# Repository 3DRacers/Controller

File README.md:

# 3DRacers Controller

The Arduino-powered controller for a 3DRacers.

This project is actually unsupported by the main development of 3DRacers, while exhist some valid alternatives:

 - A Bluetooth HID generic controller (like the cheap Android/iOS controllers available on the market)
 - A Bluetooth HID Arduino board like the Adafruit Bluefruit EZ-Key or the RedBearLab Blend Micro
 - A 3D printed remote attached to your smartphone
 
 For info about 3dracers: [www.3dracers.com](http://www.3dracers.com)
 For the 3DRacers Pilot Board schematics: [Pilot repository](https://github.com/3DRacers/PilotBoard)

License
----

Creative Commons Share-Alike 4.0

**Open Hardware, Hell Yeah!**

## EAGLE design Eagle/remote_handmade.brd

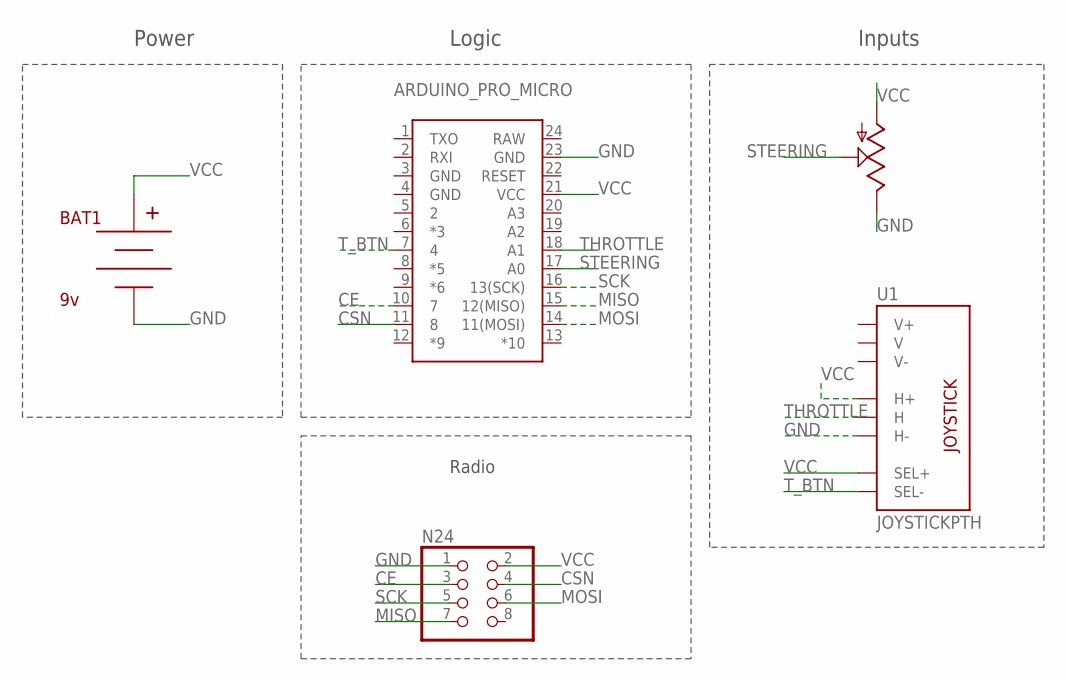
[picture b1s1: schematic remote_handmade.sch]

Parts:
ARDUINO_PRO_MICRO: ARDUINO_PRO_MICRONORMALNORMAL; ARDUINO_PRO_MICRO
BAT1: 9v; BC9VPC
N24: NRF24; 2X04
RV1: POT; ALPS_POT
U1: JOYSTICKPTH; JOYSTICK

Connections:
CE: ARDUINO_PRO_MICRO.10 (7), N24.3
CSN: ARDUINO_PRO_MICRO.11 (8), N24.4
GND: ARDUINO_PRO_MICRO.23 (GND), BAT1.V-, N24.1, RV1.P$1 (E), U1.H3 (H-)
MISO: ARDUINO_PRO_MICRO.15 (12(MISO)), N24.7
MOSI: ARDUINO_PRO_MICRO.14 (11(MOSI)), N24.6
SCK: ARDUINO_PRO_MICRO.16 (13(SCK)), N24.5
STEERING: ARDUINO_PRO_MICRO.17 (A0), RV1.P$2 (S)
THROTTLE: ARDUINO_PRO_MICRO.18 (A1), U1.H2 (H)
T_BTN: ARDUINO_PRO_MICRO.7 (4), U1.B2A (SEL-)
VCC: ARDUINO_PRO_MICRO.21 (VCC), BAT1.V+, N24.2, RV1.P$3 (A), U1.B1A (SEL+), U1.H1 (H+)

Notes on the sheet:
Power
Logic
Inputs
Radio

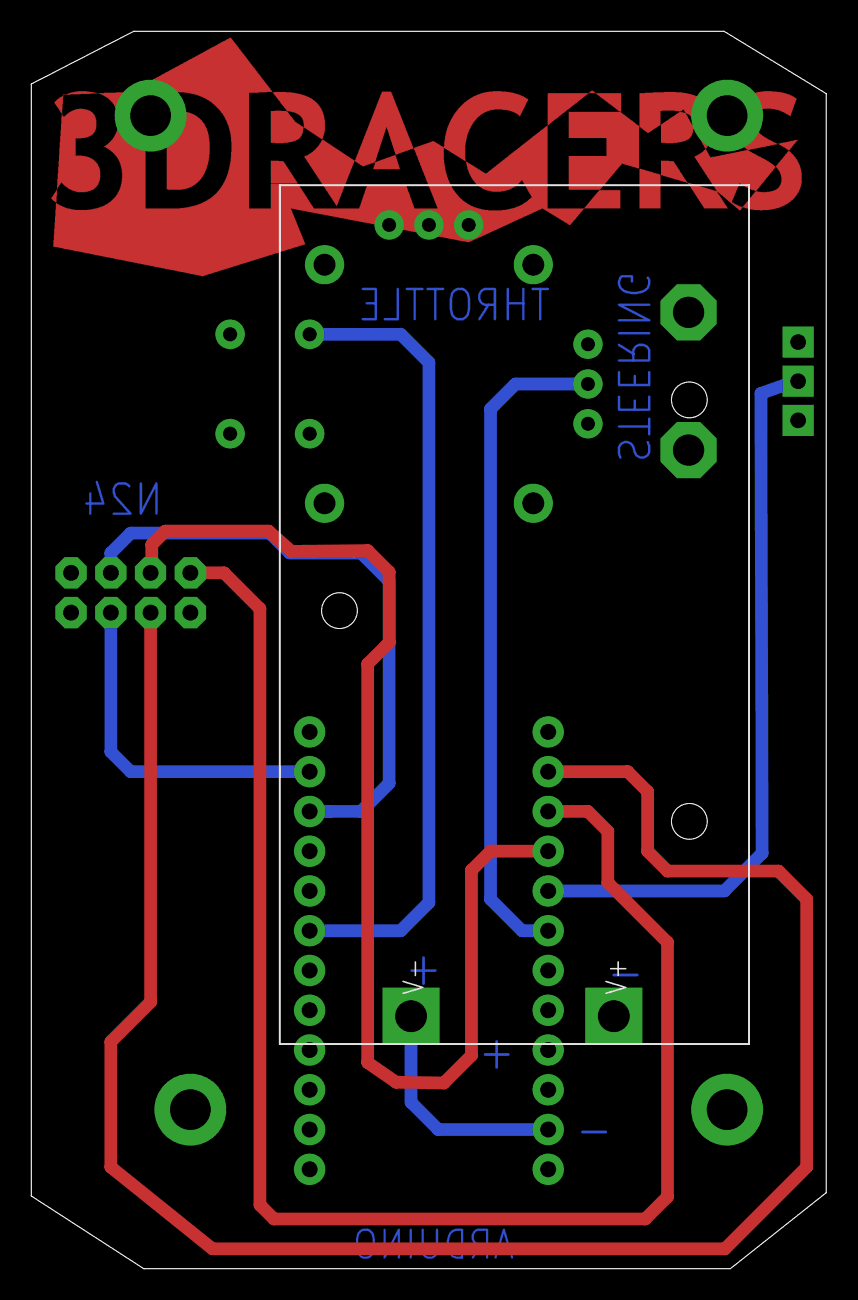
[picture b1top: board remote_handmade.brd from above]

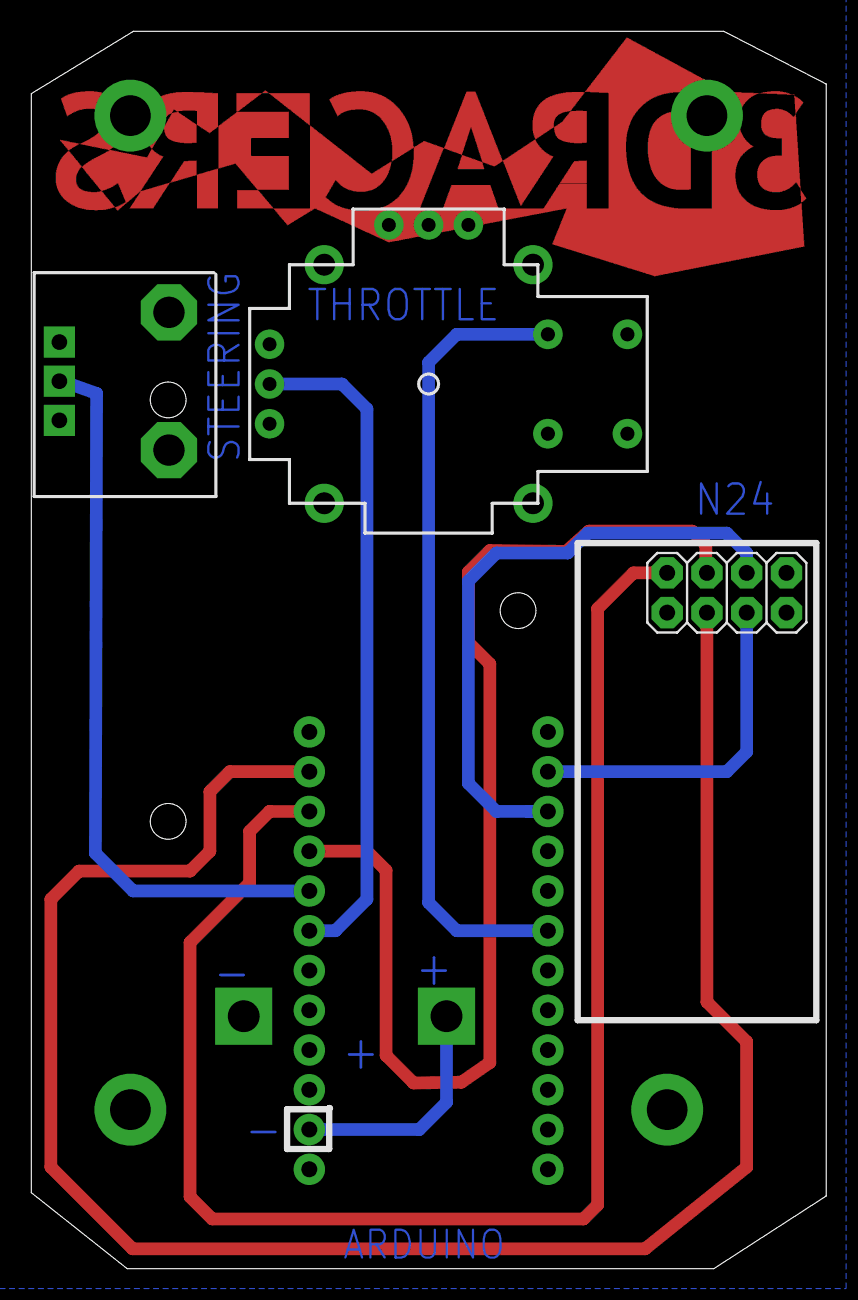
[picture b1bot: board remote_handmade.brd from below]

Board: 2 copper layers, 50.8 x 79.0 mm, 5 parts (3 on the bottom side), 10 nets.

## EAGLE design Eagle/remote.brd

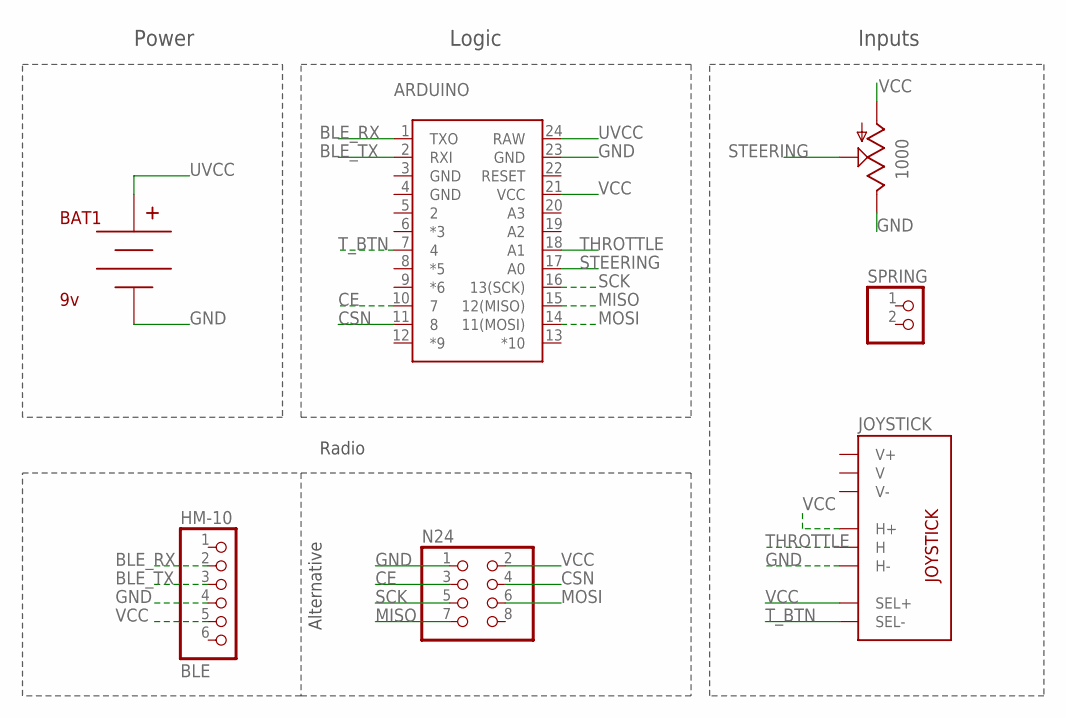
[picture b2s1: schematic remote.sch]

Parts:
ARDUINO: ARDUINO_PRO_MICRONORMALNORMAL; ARDUINO_PRO_MICRO
BAT1: 9v; BC9VPC
HM-10: BLE; 1X06-BIG
JOYSTICK: JOYSTICK
N24: NRF24; 2X04
RV1: 1000; ALPS_POT_2
SPRING: PINHD-1X2; 1X02

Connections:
BLE_RX: ARDUINO.1 (TXO), HM-10.2
BLE_TX: ARDUINO.2 (RXI), HM-10.3
CE: ARDUINO.10 (7), N24.3
CSN: ARDUINO.11 (8), N24.4
GND: ARDUINO.23 (GND), BAT1.V-, HM-10.4, JOYSTICK.H3 (H-), N24.1, RV1.P$1 (E)
MISO: ARDUINO.15 (12(MISO)), N24.7
MOSI: ARDUINO.14 (11(MOSI)), N24.6
SCK: ARDUINO.16 (13(SCK)), N24.5
STEERING: ARDUINO.17 (A0), RV1.P$2 (S)
THROTTLE: ARDUINO.18 (A1), JOYSTICK.H2 (H)
T_BTN: ARDUINO.7 (4), JOYSTICK.B2A (SEL-)
UVCC: ARDUINO.24 (RAW), BAT1.V+
VCC: ARDUINO.21 (VCC), HM-10.5, JOYSTICK.B1A (SEL+), JOYSTICK.H1 (H+), N24.2, RV1.P$3 (A)

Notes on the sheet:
Power
Logic
Inputs
Radio
Alternative

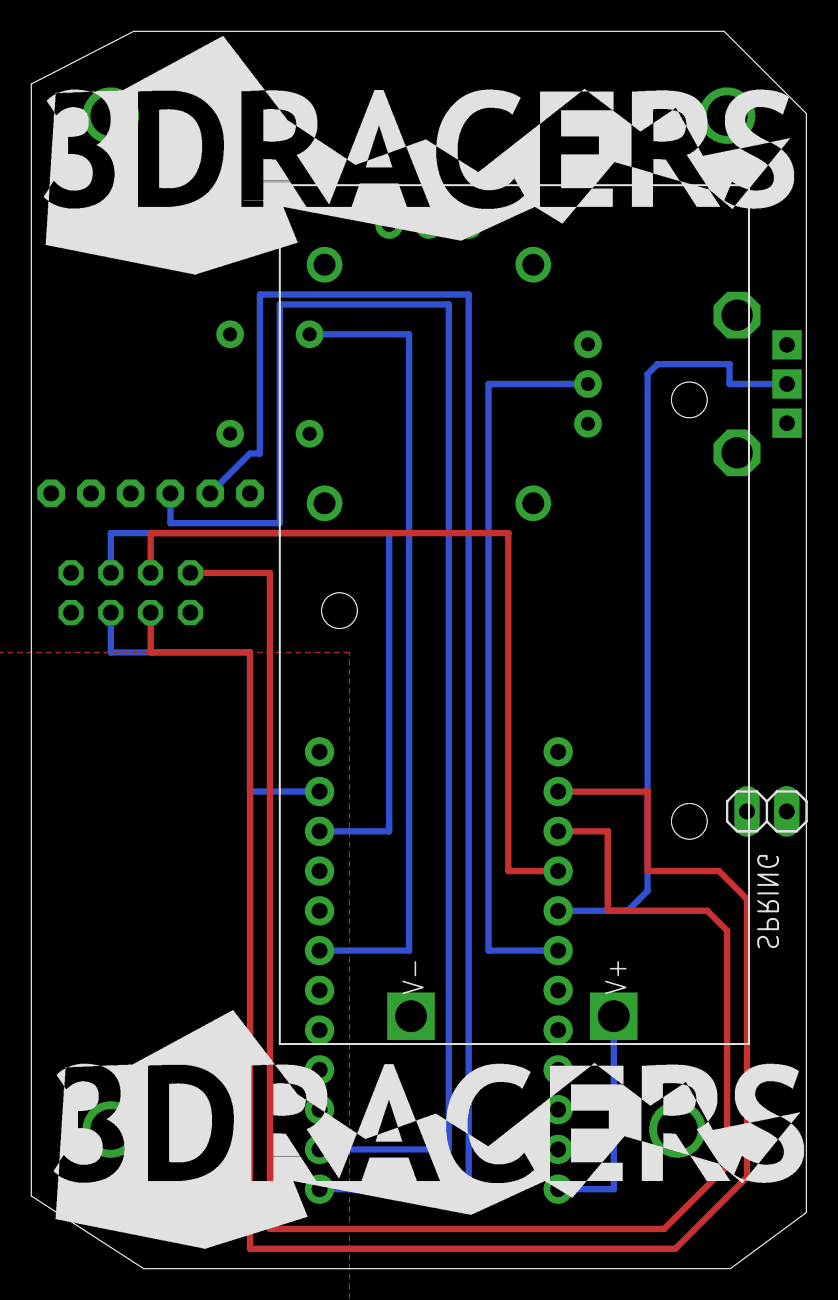
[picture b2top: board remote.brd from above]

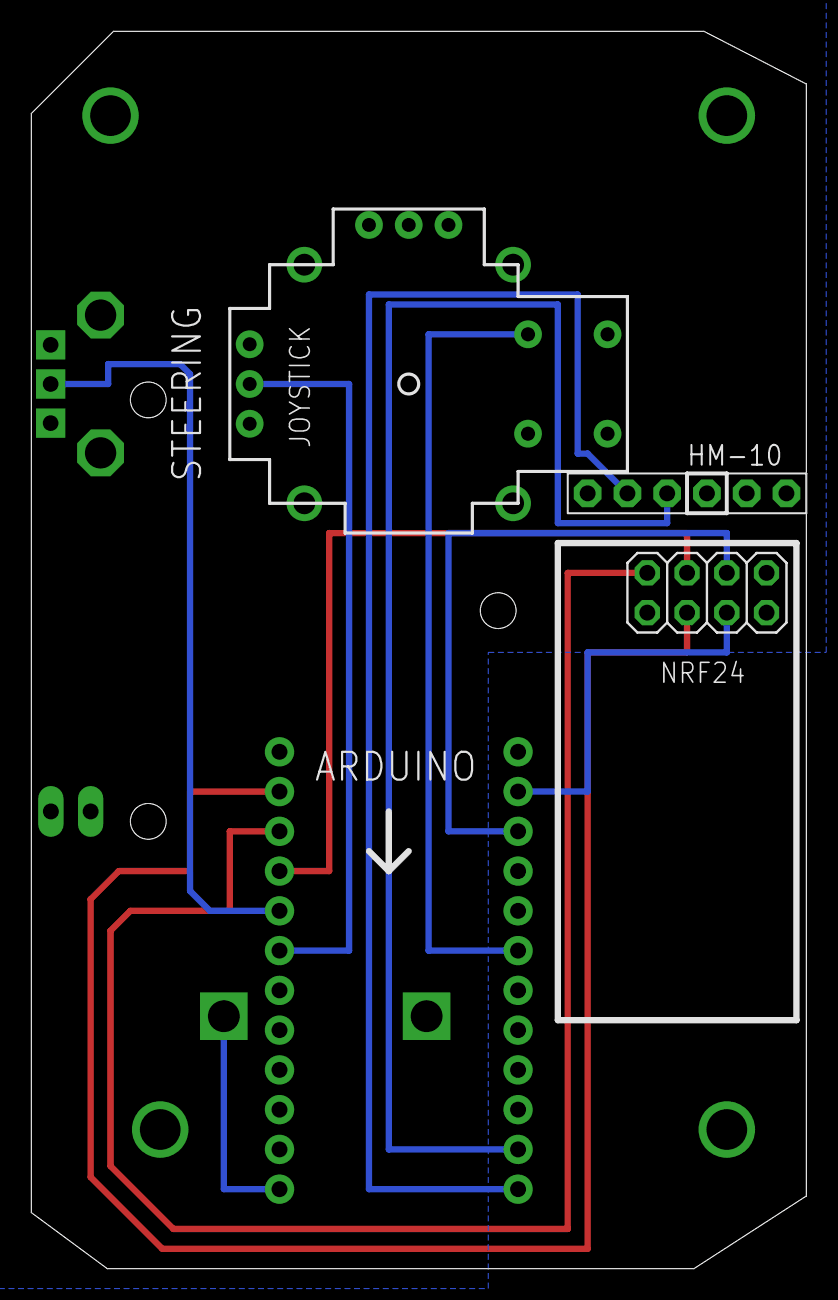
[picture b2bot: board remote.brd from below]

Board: 2 copper layers, 49.5 x 79.0 mm, 7 parts (5 on the bottom side), 13 nets.

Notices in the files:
parts and their libraries:
SparkFun-Electromechanical: Licensing: Creative Commons ShareAlike 4.0 International - https://creativecommons.org/licenses/by-sa/4.0
